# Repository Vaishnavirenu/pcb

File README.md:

View this project on [CADLAB.io](https://cadlab.io/project/29274). 

# pcb

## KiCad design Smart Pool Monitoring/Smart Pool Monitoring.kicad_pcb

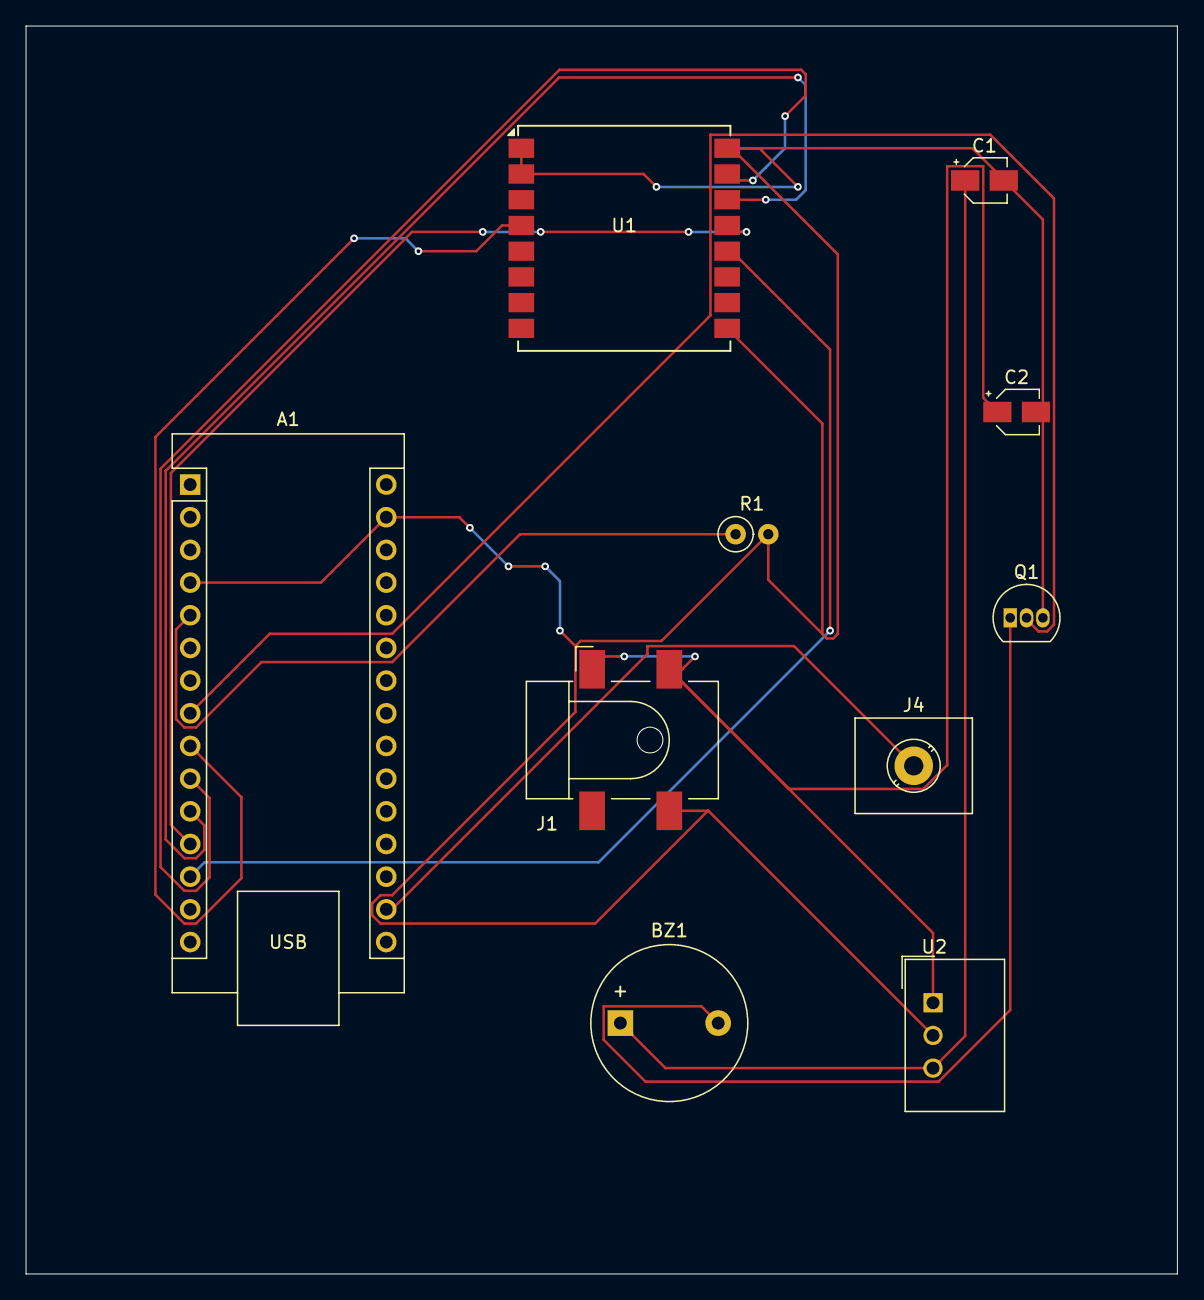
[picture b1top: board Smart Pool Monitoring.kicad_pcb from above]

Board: 2 copper layers, 89.5 x 97.0 mm, 10 parts (0 on the bottom side), 12 nets.

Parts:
A1: Arduino_Nano_Every; Arduino_Nano
BZ1: Buzzer; Buzzer_12x9.5RM7.6
C1, C2: C; CP_Elec_3x5.3
J1: Barrel_Jack; BarrelJack_CLIFF_FC681465S_SMT_Horizontal
J4: Screw_Terminal_01x02; TerminalBlock_MetzConnect_360271_1x01_Horizontal_ScrewM3.0_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
Q1: BC547; TO-92_Inline
R1: R; R_Axial_DIN0207_L6.3mm_D2.5mm_P2.54mm_Vertical
U1: Ai-Thinker-Ra-02; Ai-Thinker-Ra-01-LoRa
U2: L7805; Converter_DCDC_TRACO_TSR1-xxxxE_THT

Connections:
GND: A1.4 (GND), A1.29 (GND), C1.2, C2.2, J1.2, Q1.3 (E), R1.2, U1.1 (GND), U1.2 (GND), U1.9 (GND), U1.16 (GND), U2.2 (GND)
unnamed: A1.17 (3V3), J4.1
unnamed: A1.5 (D2), R1.1
unnamed: A1.8 (D5), Q1.2 (B)
unnamed: A1.9 (D6), U1.4 (~RESET)
unnamed: A1.10 (D7), U1.15 (~NSS)
unnamed: A1.11 (D8), U1.14 (MOSI)
unnamed: A1.12 (D9), U1.13 (MISO)
unnamed: A1.13 (D10), U1.12 (SCK)
unnamed: BZ1.1 (+), C1.1, U2.3 (OUT)
unnamed: BZ1.2 (-), Q1.1 (C)
unnamed: C2.1, J1.1, U2.1 (IN)

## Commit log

2025-04-19 Backlink to CADLAB.io has been added.
